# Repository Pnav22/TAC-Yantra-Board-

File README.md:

# TAC YANTRA - 3x3 Macro Keypad with Rotary Encoder

This is a custom 9-key macro pad with a rotary encoder, powered by the XIAO RP2040 and running KMK firmware. It was a pain to make but very enlightening.

---

## Overview

Here's a picture of my work! This is a submission for HackPad!

Shaded            |  WireFrame
:-------------------------:|:-------------------------:
  |  

---

##  PCB
PCB            |  Schematic
:-------------------------:|:-------------------------:
  |  

---
## How It Fits Together

It uses HeatSet Inserts at the bottom that are secured by M3 x 16mm screws from the top.
 
---

##  Features

- 9 programmable keys (currently set to numbers `1–9`)
- EC11 rotary encoder for volume control
- Push-to-toggle Play/Pause
- KMK firmware written in Python for rapid iteration
- USB HID support (works on macOS, Windows, Linux)
  
---

## ⚙️ Bill of Materials (BOM)

| Quantity | Item                           |
|----------|--------------------------------|
| 9        | Cherry MX Switches             |
| 9        | DSA Keycaps                    |
| 4        | M3x5x4 Heatset Inserts         |
| 4        | M3x16mm Socket Head Cap Screws |
| 9        | 1N4148 DO-35 Diodes            |
| 1        | EC11 Rotary Encoder            |
| 1        | Seeed XIAO RP2040              |
| 1        | Case (2 printed parts)         |

---

##  Firmware

This project uses [KMK Firmware](https://github.com/KMKfw/kmk_firmware), a keyboard firmware built on CircuitPython. Code can be modified directly on the board via USB like a flash drive.

`code.py` handles:
- Matrix setup
- Encoder input
- Volume + media key support

---

##  TAC YANTRA - Explanation Behind The Name

**TAC YANTRA** is the name of this device:

- **TAC** – tactical 
- **YANTRA** – a Sanskrit term meaning *"instrument" or "machine"*
- 
Together, **TAC YANTRA** is  a tactical interface device. Very funny name ik ik lol. 

---

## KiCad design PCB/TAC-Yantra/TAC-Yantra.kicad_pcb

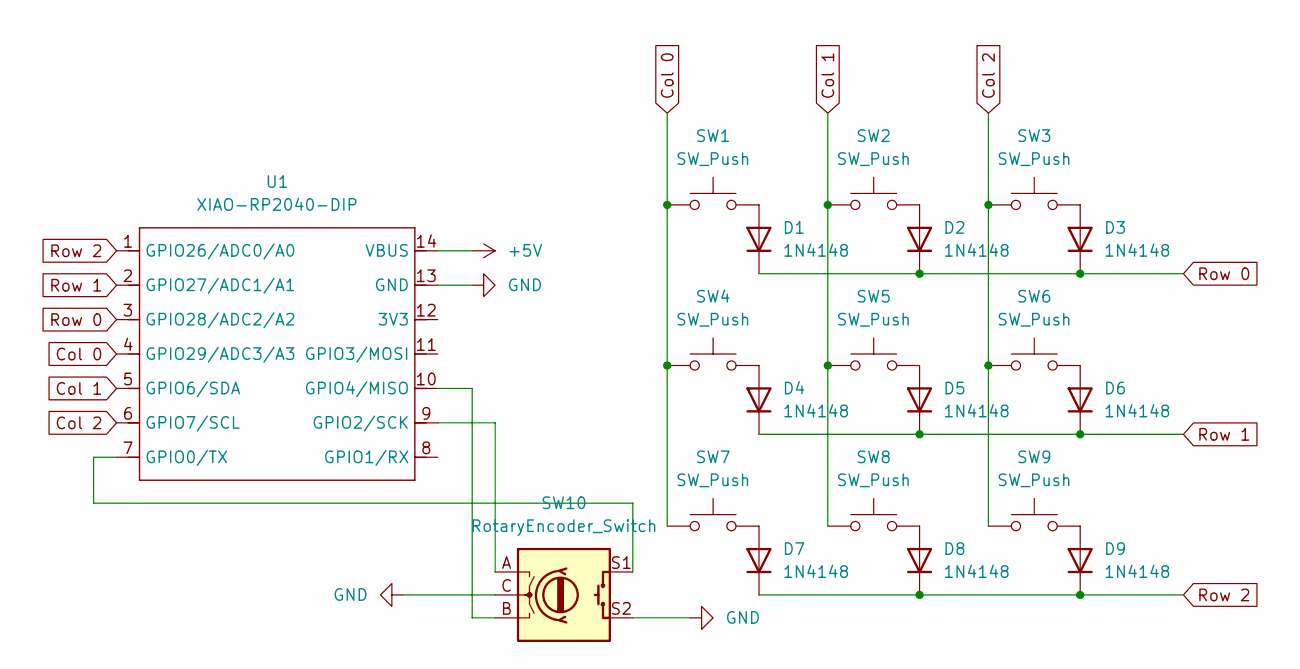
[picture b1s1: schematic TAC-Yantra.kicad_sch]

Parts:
D1, D2, D3, D4, D5, D6, D7, D8, D9: 1N4148; D_DO-35_SOD27_P7.62mm_Horizontal
SW1, SW2, SW3, SW4, SW5, SW6, SW7, SW8, SW9: SW_Push; SW_Cherry_MX_1.00u_PCB
SW10: RotaryEncoder_Switch; RotaryEncoder_Alps_EC11E-Switch_Vertical_H20mm
U1: XIAO-RP2040-DIP

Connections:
+5V: U1.14 (VBUS)
Col 0: SW1.1, SW4.1, SW7.1, U1.4 (GPIO29/ADC3/A3)
Col 1: SW2.1, SW5.1, SW8.1, U1.5 (GPIO6/SDA)
Col 2: SW3.1, SW6.1, SW9.1, U1.6 (GPIO7/SCL)
GND: SW10.C, SW10.S2, U1.13 (GND)
unnamed: D1.2 (A), SW1.2
unnamed: D2.2 (A), SW2.2
unnamed: D3.2 (A), SW3.2
unnamed: D4.2 (A), SW4.2
unnamed: D5.2 (A), SW5.2
unnamed: D6.2 (A), SW6.2
unnamed: D7.2 (A), SW7.2
unnamed: D8.2 (A), SW8.2
unnamed: D9.2 (A), SW9.2
unnamed: SW10.S1, U1.7 (GPIO0/TX)
unnamed: SW10.A, U1.9 (GPIO2/SCK)
unnamed: SW10.B, U1.10 (GPIO4/MISO)
Row 0: D1.1 (K), D2.1 (K), D3.1 (K), U1.3 (GPIO28/ADC2/A2)
Row 1: D4.1 (K), D5.1 (K), D6.1 (K), U1.2 (GPIO27/ADC1/A1)
Row 2: D7.1 (K), D8.1 (K), D9.1 (K), U1.1 (GPIO26/ADC0/A0)

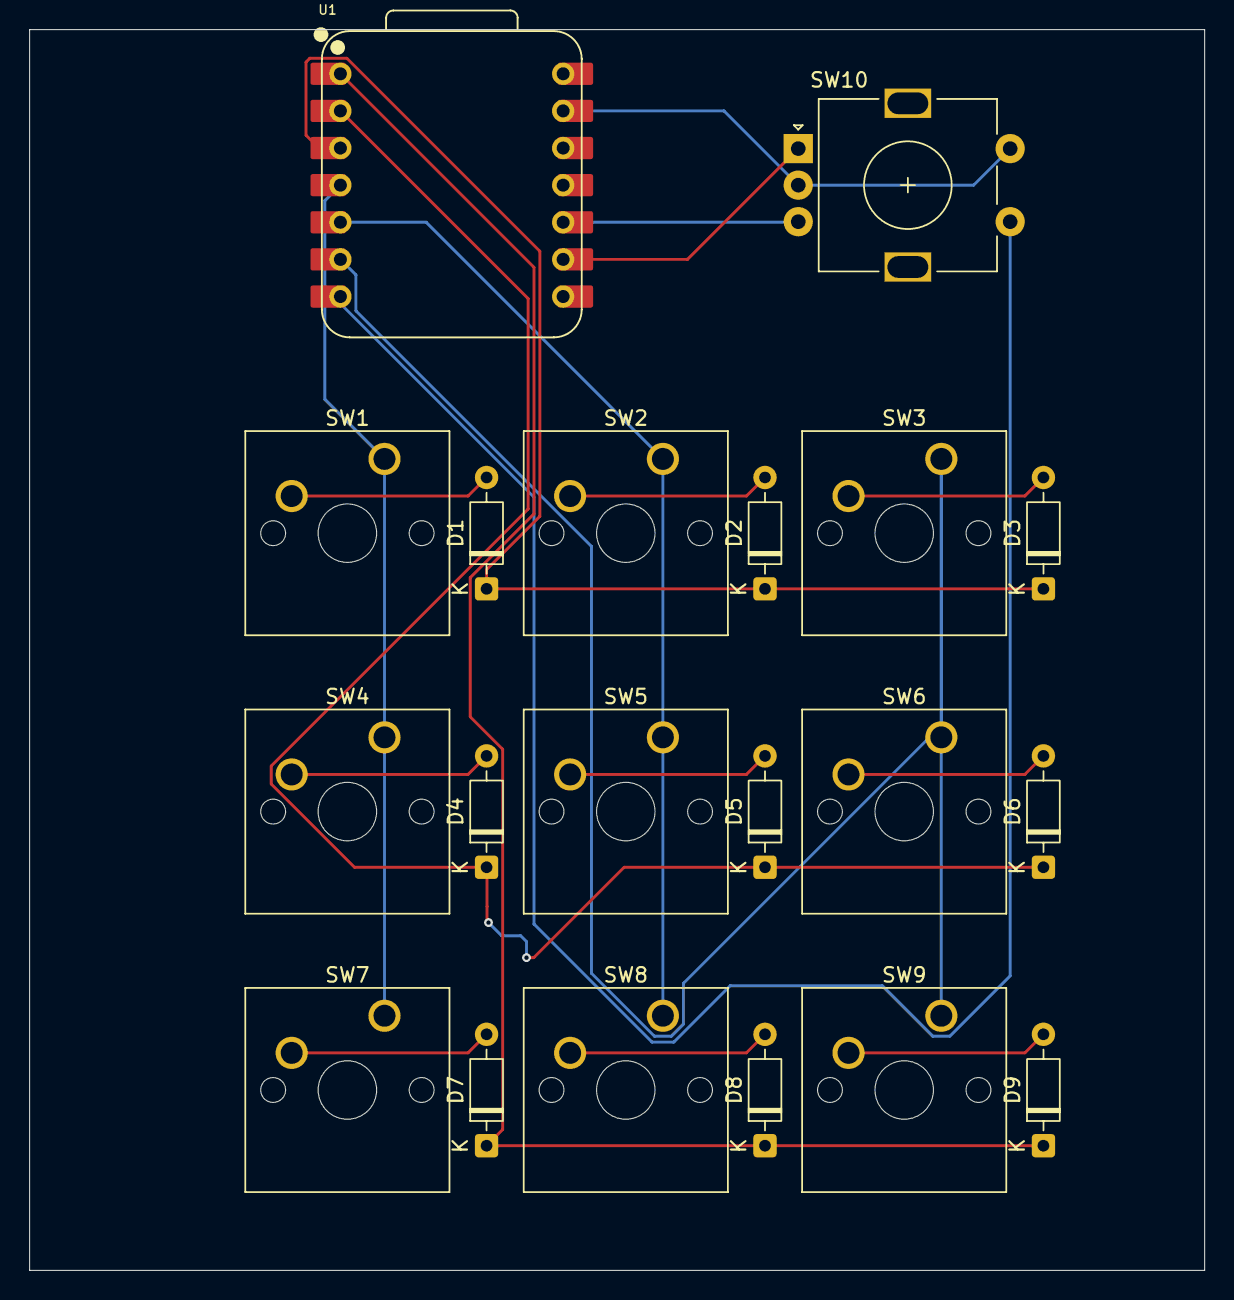
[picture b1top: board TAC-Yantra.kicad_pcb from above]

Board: 2 copper layers, 80.4 x 84.9 mm, 20 parts (0 on the bottom side), 19 nets.

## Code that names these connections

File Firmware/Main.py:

import board
from kmk.kmk_keyboard import KMKKeyboard
from kmk.scanners import DiodeOrientation
from kmk.scanners.keypad import MatrixScanner
from kmk.keys import KC
from kmk.modules.encoder import EncoderHandler
from kmk.modules.layers import Layers

keyboard = KMKKeyboard()

# === Encoder support ===
encoder_handler = EncoderHandler()
keyboard.modules.append(encoder_handler)

# === Optional: Layer support (not used yet) ===
layers = Layers()
keyboard.modules.append(layers)

# === Define matrix ===
keyboard.matrix = MatrixScanner(
    cols=(board.MISO, board.SCK, board.SDA),  # Cols: GPIO4, GPIO5, GPIO6
    rows=(board.A1, board.A2, board.A0),      # Rows: GPIO27, GPIO28, GPIO26
    diode_orientation=DiodeOrientation.COL2ROW
)

# === Rotary Encoder Pins ===
encoder_handler.pins = ((board.GP0, board.GP1),)  # CLK, DT
encoder_handler.map = [
    ((KC.VOLD, KC.VOLU),),  # Rotate left/right
]

# === Define keymap ===
keyboard.keymap = [
    [
        KC.N1, KC.N2, KC.N3,   # Row 0
        KC.N4, KC.N5, KC.N6,   # Row 1
        KC.N7, KC.N8, KC.N9,   # Row 2
        KC.MPLY               # Encoder button (GPIO7, assumed last in scan list)
    ]
]

# === Run KMK ===
if __name__ == '__main__':
    keyboard.go()

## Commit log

2025-06-24 added files
    added files
2025-06-24 Added PCB Files
2025-06-24 added gerbers
2025-06-24 added top n botoom cad
